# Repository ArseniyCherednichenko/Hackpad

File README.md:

# Arseniy's HackPad

My Hackpad is a 3×3 macro keypad, which can be programmed to address all needs. It runs on a Seeed XIAO RP2040, and features Cherry MX mechanical switches, SK6812 RGB LEDs, a rotary encoder, and an OLED status display.

## Why I built this

I wanted to have a custom keypad on my desk and use shortcuts assigned to each key to simplify and make my workflow more efficient.

---
<!--
## Pin Assignments
| Signal       | XIAO Pin | Description                       |
|-------------|----------|-----------------------------------|
| ROW0        | D0       | Switch matrix row 0               |
| ROW1        | D1       | Switch matrix row 1               |
| ROW2        | D2       | Switch matrix row 2               |
| COL0        | D3       | Switch matrix column 0            |
| COL1        | D6       | Switch matrix column 1            |
| COL2        | D7       | Switch matrix column 2            |
| OLED SDA    | D4       | I²C data for SSD1306 display      |
| OLED SCL    | D5       | I²C clock for SSD1306 display     |
| ENC_A       | D8       | Rotary encoder channel A          |
| ENC_B       | D9       | Rotary encoder channel B          |
| LED_DATA    | D10      | SK6812 data chain                 |

---

-->
## Usage

To use Hackpad, order the PCB using `gerbers.zip` from JLCPCB, print the 3D enclosure, solder the components, install firmware and assemble everything. Edit `main.py` to customise your keymap.

## Schematic

---

## PCB 

---

## Files Layout

```
PCB/
  hackpad.kicad_pro     
  hackpad.kicad_sch
  hackpad.kicad_prl
  hackpad.kicad_pcb
  gerbers.zip    
CAD/
  Hackpad Keyboard Outline.step
  Hackpad PCB.step
  Hackpad case BOTTOM.step
  Hackpad case TOP.step
  Hackpad case FULL.step
Firmware/
  main.py               
images/
  (screenshots)
BOM.csv
README.md
```

---

## PCB Fabrication Notes

- Board size: **80 × 70 mm**, 2 layers, 1.6 mm FR4
- Min trace width: 0.2 mm (signal), 0.5 mm (power)
- Min via: 0.8 mm drill, 0.4 mm annular ring
- Surface finish: HASL or ENIG

---

## Case Printing Notes

- Print `Hackpad case TOP.step`, `Hackpad case BOTTOM.step` and `Hackpad Keyboard Outline.step` in PLA or PETG, 0.2 mm layer height, 3–4 perimeters.
- Insert M3 heat-set inserts into the four corner bosses of the bottom tray using a soldering iron.
- PCB sits on the 2 mm standoffs inside the tray.
- Top plate secures with 4× M3×8 screws through the corner holes.
  
---

## Bill of Materials

| # | Component | Qty | Package | Supplier | Link | Price (€) |
|---|-----------|-----|---------|----------|------|-----------|
| 1 | Seeed XIAO RP2040 | 1 | DIP-14 (castellated) | AliExpress | [Buy](https://de.aliexpress.com/item/1005008200917480.html) | 5.49 |
| 2 | Cherry MX Compatible Switch | 9 | MX Hotswap 1U | Amazon | [Buy](https://www.amazon.de/Topiky-Mechanische-Tastaturschalter-Keyboard-Mounted-default/dp/B086MQXQW7) | 7.23 |
| 3 | SK6812 MINI-E RGB LED | 9 | Reverse-mount 3228 | AliExpress | [Buy](https://de.aliexpress.com/item/1005008308801366.html) | 4.82 |
| 4 | 1N4148 Diode | 9 | DO-35 (THT) | AliExpress | [Buy](https://de.aliexpress.com/item/1005009372401863.html) | 1.49 |
| 5 | EC11 Rotary Encoder | 1 | Alps EC11E, vertical, 20mm | AliExpress | [Buy](https://de.aliexpress.com/item/1005008036285937.html) | 5.18 |
| 6 | 0.91" OLED Display (SSD1306) | 1 | 4-pin I2C, 128×32 | AliExpress | [Buy](https://de.aliexpress.com/item/1005010665352578.html) | 7.11 |
| 7 | Encoder Knob | 1 | 6mm D-shaft | AliExpress | [Buy](https://de.aliexpress.com/item/4000027546987.html) | 3.76 |
| 8 | MX Keycaps (1U) | 9 | MX stem compatible | AliExpress | [Buy](https://de.aliexpress.com/item/1005010020786682.html) | 8.20 |
| 9 | M2.5×6mm Screws | 4 | M2.5 pan head | Moddiy | [Buy](https://www.moddiy.com/products/1268/M2.5-x-6mm-Black-Screws-CM2.5x6x4.5.html) | 0.69 |
| 10 | M2.5×4mm Standoffs | 4 | M2.5 female-female | Amazon | [Buy](https://www.amazon.de/Standoff-Schraube-Computer-Motherboard-Weiblich/dp/B0CCQBQHJQ) | 7.28 |
| 11 | Rubber Feet (adhesive) | 4 | ~8mm diameter | AliExpress | [Buy](https://de.aliexpress.com/item/1005007854664253.html) | 3.83 |
| 12 | USB-C Cable | 1 | USB-C to USB-A/C | AliExpress | [Buy](https://de.aliexpress.com/item/1005004784212304.html) | 1.93 |
| | | | | | **TOTAL** | **€32.80** |

---

*Built with ❤️ by Arseniy*

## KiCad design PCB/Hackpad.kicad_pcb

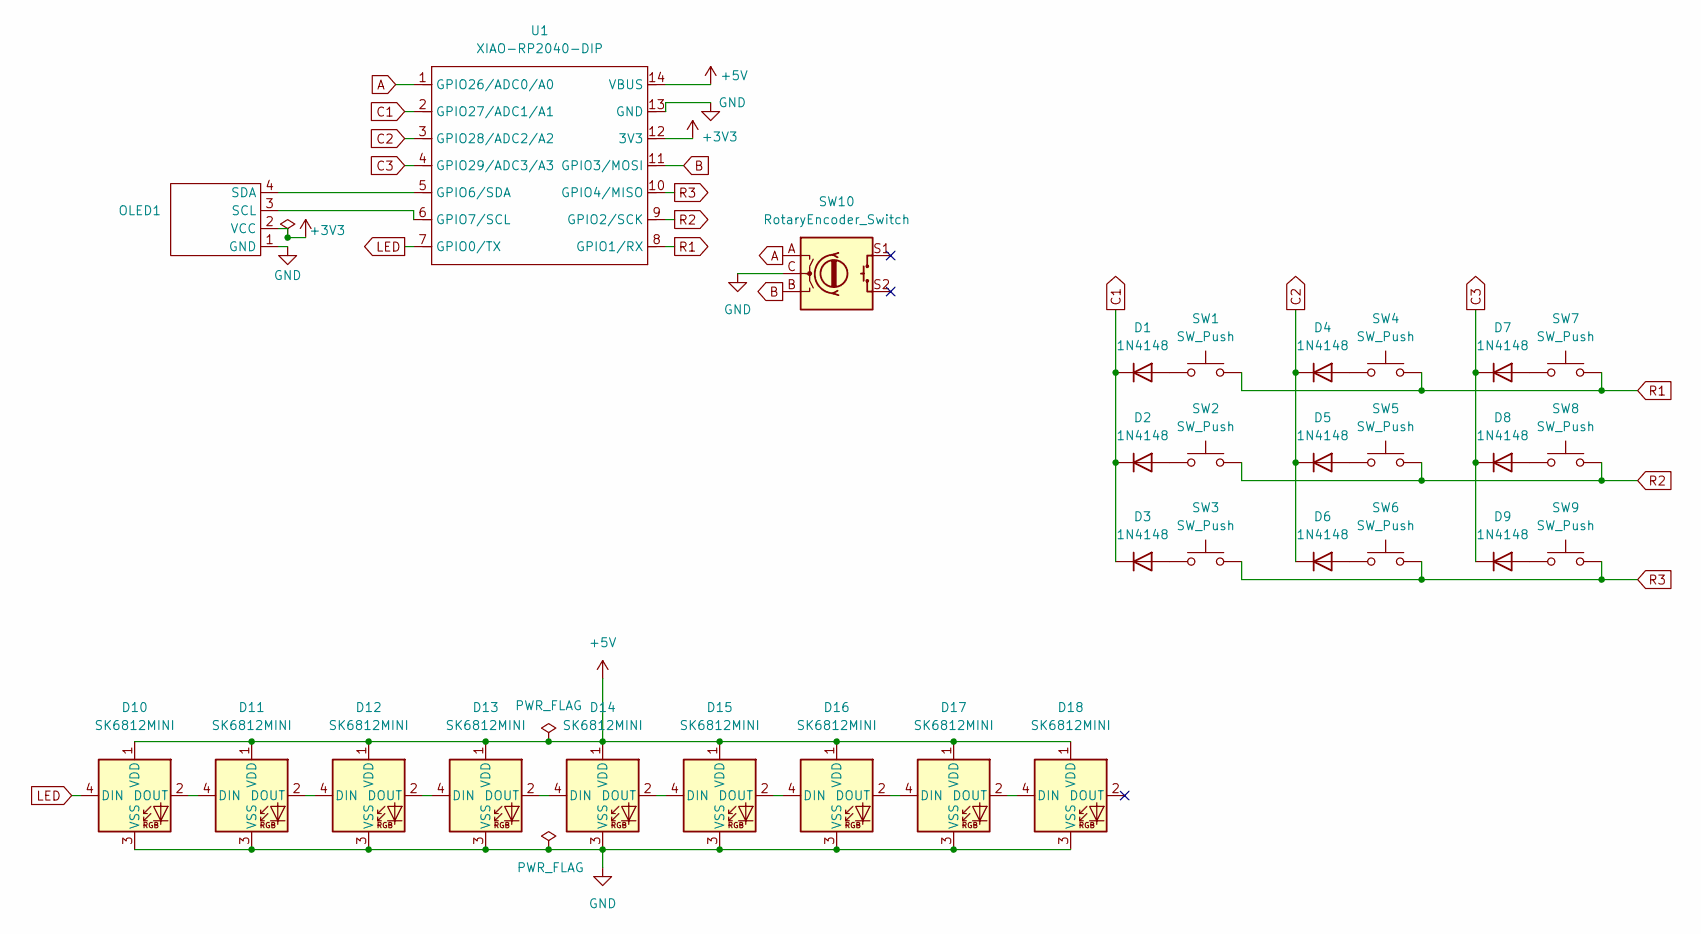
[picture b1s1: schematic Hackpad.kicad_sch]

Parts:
D1, D2, D3, D4, D5, D6, D7, D8, D9: 1N4148; D_DO-35_SOD27_P7.62mm_Horizontal
D10, D11, D12, D13, D14, D15, D16, D17, D18: SK6812MINI; MX_SK6812MINI-E_REV
OLED1: SSD1306-0.91-OLED-4pin-128x32
SW1, SW2, SW3, SW4, SW5, SW6, SW7, SW8, SW9: SW_Push; MX-Hotswap-1U
SW10: RotaryEncoder_Switch; RotaryEncoder_Alps_EC11E-Switch_Vertical_H20mm
U1: XIAO-RP2040-DIP

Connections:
+3V3: OLED1.2 (VCC), U1.12 (3V3)
+5V: D10.1 (VDD), D11.1 (VDD), D12.1 (VDD), D13.1 (VDD), D14.1 (VDD), D15.1 (VDD), D16.1 (VDD), D17.1 (VDD), D18.1 (VDD), U1.14 (VBUS)
A: SW10.A, U1.1 (GPIO26/ADC0/A0)
B: SW10.B, U1.11 (GPIO3/MOSI)
C1: D1.1 (K), D2.1 (K), D3.1 (K), U1.2 (GPIO27/ADC1/A1)
C2: D4.1 (K), D5.1 (K), D6.1 (K), U1.3 (GPIO28/ADC2/A2)
C3: D7.1 (K), D8.1 (K), D9.1 (K), U1.4 (GPIO29/ADC3/A3)
GND: D10.3 (VSS), D11.3 (VSS), D12.3 (VSS), D13.3 (VSS), D14.3 (VSS), D15.3 (VSS), D16.3 (VSS), D17.3 (VSS), D18.3 (VSS), OLED1.1 (GND), SW10.C, U1.13 (GND)
LED: D10.4 (DIN), U1.7 (GPIO0/TX)
unnamed: D1.2 (A), SW1.2
unnamed: D2.2 (A), SW2.2
unnamed: D3.2 (A), SW3.2
unnamed: D4.2 (A), SW4.2
unnamed: D5.2 (A), SW5.2
unnamed: D6.2 (A), SW6.2
unnamed: D7.2 (A), SW7.2
unnamed: D8.2 (A), SW8.2
unnamed: D9.2 (A), SW9.2
unnamed: D10.2 (DOUT), D11.4 (DIN)
unnamed: D11.2 (DOUT), D12.4 (DIN)
unnamed: D12.2 (DOUT), D13.4 (DIN)
unnamed: D13.2 (DOUT), D14.4 (DIN)
unnamed: D14.2 (DOUT), D15.4 (DIN)
unnamed: D15.2 (DOUT), D16.4 (DIN)
unnamed: D16.2 (DOUT), D17.4 (DIN)
unnamed: D17.2 (DOUT), D18.4 (DIN)
unnamed: OLED1.3 (SCL), U1.6 (GPIO7/SCL)
unnamed: OLED1.4 (SDA), U1.5 (GPIO6/SDA)
R1: SW1.1, SW4.1, SW7.1, U1.8 (GPIO1/RX)
R2: SW2.1, SW5.1, SW8.1, U1.9 (GPIO2/SCK)
R3: SW3.1, SW6.1, SW9.1, U1.10 (GPIO4/MISO)

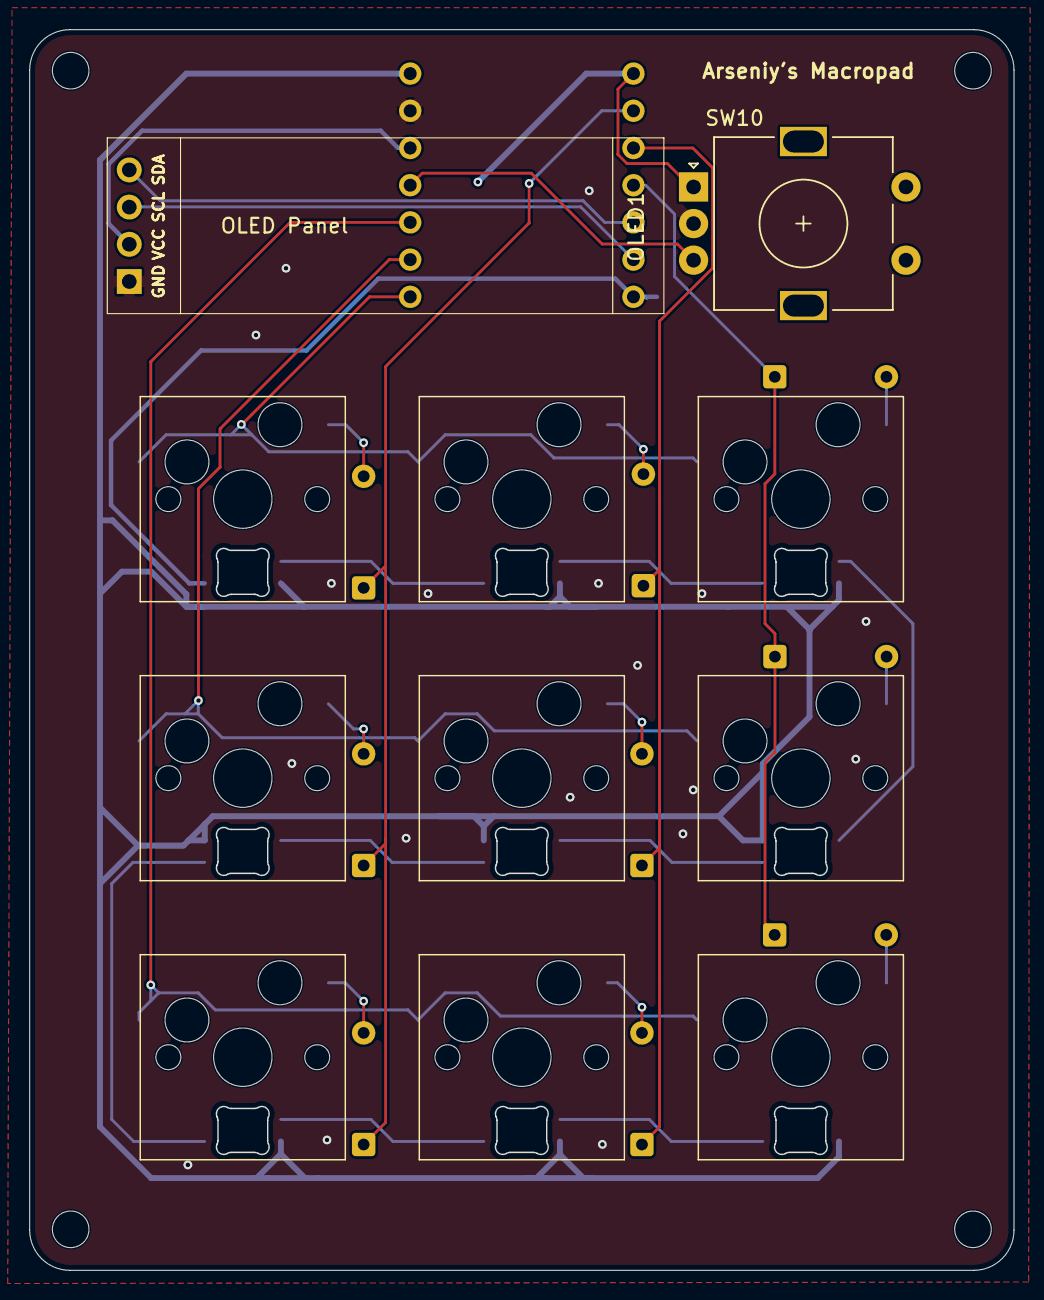
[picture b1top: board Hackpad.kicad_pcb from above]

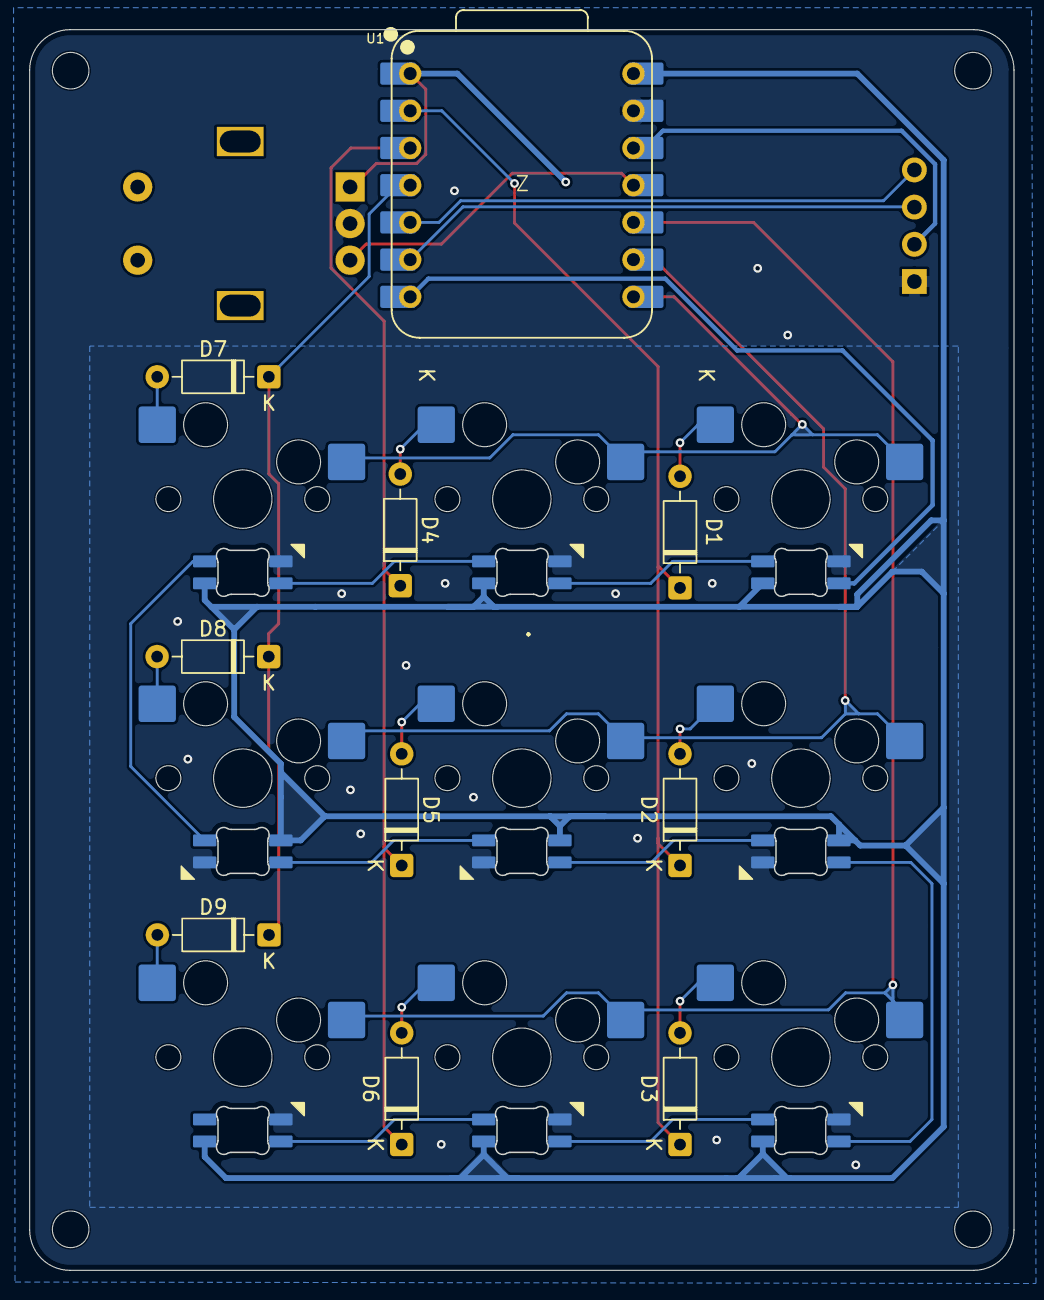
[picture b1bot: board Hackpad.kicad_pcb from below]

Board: 2 copper layers, 67.2 x 84.7 mm, 30 parts (19 on the bottom side), 31 nets.

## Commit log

2026-03-28 Create f
2026-03-29 Revise README for clarity and feature explanation
    Updated README.md to clarify project details and features.
2026-03-29 Create j
2026-03-29 Rename Screenshot 2026-03-29 at 20.05.30.png to CAD
2026-03-29 Rename Screenshot 2026-03-29 at 20.06.04.png to CAD back
2026-03-29 Rename Screenshot 2026-03-29 at 21.07.40.png to PCB
2026-03-29 Rename Screenshot 2026-03-29 at 21.07.59.png to Schematic
2026-03-29 Revise README for clarity and add new sections
    Updated the README to correct the wording from 'coded' to 'programmed' and added sections for Schematic and PCB with images. Expanded the Bill of Materials with detailed component listings and links.
2026-03-29 Fix typo in Hackpad description
2026-03-29 Revise README with project name and details
    Updated project name and enhanced description for clarity. Revised case printing notes and added detailed bill of materials.
2026-03-29 Add usage section to README
    Added usage instructions for Hackpad setup and customization.
